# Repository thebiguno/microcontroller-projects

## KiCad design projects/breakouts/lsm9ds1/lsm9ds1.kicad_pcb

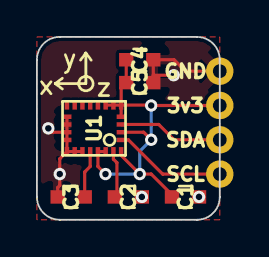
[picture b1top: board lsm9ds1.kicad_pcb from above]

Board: 2 copper layers, 10.2 x 10.2 mm, 7 parts (0 on the bottom side), 6 nets.

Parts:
C1, C2, C4: 100nF; C_0603
C3: 10nF; C_0603
C5: 10uF; C_0603
P1: CONN_01X04; Pin_Header_Straight_1x04
U1: LSM9DS1; LGA-24L

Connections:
+3V3: C1.1, C4.1, C5.1, P1.2, U1.1, U1.3, U1.5, U1.6, U1.7, U1.8, U1.22, U1.23
/SCL: P1.4, U1.2
/SDA: P1.3, U1.4
GND: C1.2, C2.2, C3.2, C4.2, C5.2, P1.1, U1.14, U1.15, U1.16, U1.17, U1.18, U1.19, U1.20
unnamed: C2.1, U1.24
unnamed: C3.1, U1.21

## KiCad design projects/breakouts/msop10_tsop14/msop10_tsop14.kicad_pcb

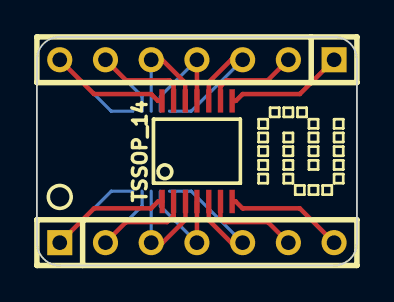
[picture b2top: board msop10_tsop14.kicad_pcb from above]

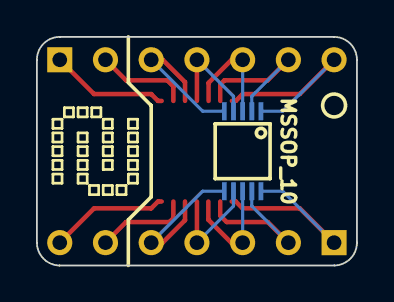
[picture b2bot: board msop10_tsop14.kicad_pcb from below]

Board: 2 copper layers, 17.8 x 12.7 mm, 6 parts (2 on the bottom side), 14 nets.

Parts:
K1, K2: PINS_7; SIL-7
K3: MSSOP_10; MSOP10-0.5
K4: TSSOP_14; TSSOP14
VAL: REF; DIGITALCAVE_LOGO
VAL#2: REF; DIGITALCAVE_LOGO

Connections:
unnamed: K2.2, K4.9
unnamed: K2.1, K4.8
unnamed: K1.7, K4.7
unnamed: K1.6, K4.6
unnamed: K2.3, K3.5, K4.10
unnamed: K1.5, K3.6, K4.5
unnamed: K1.4, K3.7, K4.4
unnamed: K2.4, K3.4, K4.11
unnamed: K2.5, K3.3, K4.12
unnamed: K2.6, K3.2, K4.13
unnamed: K2.7, K3.1, K4.14
unnamed: K1.3, K3.8, K4.3
unnamed: K1.2, K3.9, K4.2
unnamed: K1.1, K3.10, K4.1

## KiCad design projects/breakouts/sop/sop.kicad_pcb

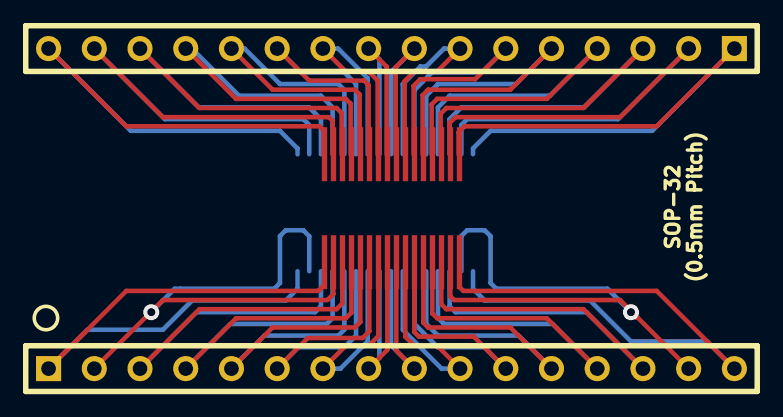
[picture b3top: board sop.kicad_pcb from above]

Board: 2 copper layers, 4 parts (1 on the bottom side), 32 nets.

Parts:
K1: PINS_32; SOP-32_05
K2: PINS_32; SOP-32_065
K3, K4: PINS_16; SIL-16

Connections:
unnamed: K1.32, K2.1, K4.16
unnamed: K1.31, K2.2, K4.15
unnamed: K1.30, K2.3, K4.14
unnamed: K1.29, K2.4, K4.13
unnamed: K1.28, K2.5, K4.12
unnamed: K1.27, K2.6, K4.11
unnamed: K1.26, K2.7, K4.10
unnamed: K1.25, K2.8, K4.9
unnamed: K1.15, K2.18, K3.15
unnamed: K1.5, K2.28, K3.5
unnamed: K1.14, K2.19, K3.14
unnamed: K1.4, K2.29, K3.4
unnamed: K1.24, K2.9, K4.8
unnamed: K1.23, K2.10, K4.7
unnamed: K1.13, K2.20, K3.13
unnamed: K1.3, K2.30, K3.3
unnamed: K1.22, K2.11, K4.6
unnamed: K1.12, K2.21, K3.12
unnamed: K1.2, K2.31, K3.2
unnamed: K1.21, K2.12, K4.5
unnamed: K1.11, K2.22, K3.11
unnamed: K1.1, K2.32, K3.1
unnamed: K1.20, K2.13, K4.4
unnamed: K1.10, K2.23, K3.10
unnamed: K1.19, K2.14, K4.3
unnamed: K1.9, K2.24, K3.9
unnamed: K1.18, K2.15, K4.2
unnamed: K1.8, K2.25, K3.8
unnamed: K1.17, K2.16, K4.1
unnamed: K1.7, K2.26, K3.7
unnamed: K1.16, K2.17, K3.16
unnamed: K1.6, K2.27, K3.6

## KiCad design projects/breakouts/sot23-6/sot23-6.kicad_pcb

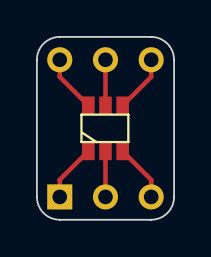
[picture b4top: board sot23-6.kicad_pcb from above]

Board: 2 copper layers, 7.6 x 10.2 mm, 3 parts (0 on the bottom side), 6 nets.

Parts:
K1: PINS_6; SOT23_6
K2, K3: PINS_3; SIL-3

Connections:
unnamed: K1.1, K2.1
unnamed: K1.2, K2.2
unnamed: K1.3, K2.3
unnamed: K1.4, K3.3
unnamed: K1.5, K3.2
unnamed: K1.6, K3.1

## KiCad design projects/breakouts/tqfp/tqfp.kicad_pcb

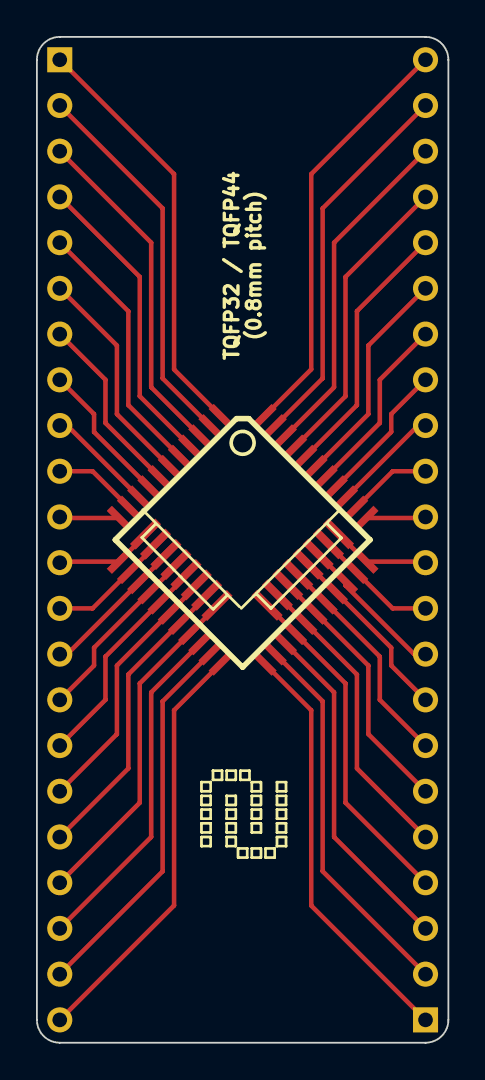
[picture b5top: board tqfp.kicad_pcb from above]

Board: 2 copper layers, 22.9 x 55.9 mm, 5 parts (0 on the bottom side), 16 nets.

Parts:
K1: PINS_44; TQFP44
K2, K3: PINS_22; SIL-18
K4: PINS_32; TQFP32
VAL: REF; DIGITALCAVE_LOGO

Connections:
unnamed: K1.30, K4.21
unnamed: K1.13, K4.10
unnamed: K1.32, K4.23
unnamed: K1.12, K4.9
unnamed: K1.31, K4.22
unnamed: K1.33, K4.24
unnamed: K1.29, K4.20
unnamed: K1.19, K4.16
unnamed: K1.28, K4.19
unnamed: K1.18, K4.15
unnamed: K1.27, K4.18
unnamed: K1.17, K4.14
unnamed: K1.26, K4.17
unnamed: K1.16, K4.13
unnamed: K1.15, K4.12
unnamed: K1.14, K4.11

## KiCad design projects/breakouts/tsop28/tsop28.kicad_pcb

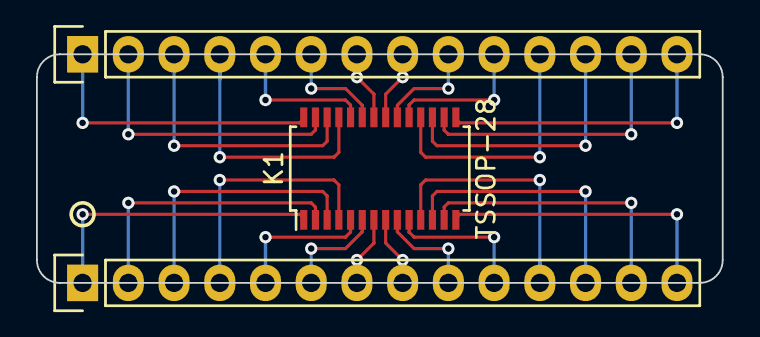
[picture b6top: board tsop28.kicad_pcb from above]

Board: 2 copper layers, 38.1 x 12.7 mm, 3 parts (0 on the bottom side), 28 nets.

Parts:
K1: TSSOP-28; TSSOP-28_4.4x9.7mm_Pitch0.65mm
K2, K3: DIP; Pin_Header_Straight_1x14

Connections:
unnamed: K1.1, K2.1
unnamed: K1.2, K2.2
unnamed: K1.3, K2.3
unnamed: K1.4, K2.4
unnamed: K1.5, K2.5
unnamed: K1.6, K2.6
unnamed: K1.7, K2.7
unnamed: K1.8, K2.8
unnamed: K1.9, K2.9
unnamed: K1.10, K2.10
unnamed: K1.11, K2.11
unnamed: K1.12, K2.12
unnamed: K1.13, K2.13
unnamed: K1.14, K2.14
unnamed: K1.15, K3.14
unnamed: K1.16, K3.13
unnamed: K1.17, K3.12
unnamed: K1.18, K3.11
unnamed: K1.19, K3.10
unnamed: K1.20, K3.9
unnamed: K1.21, K3.8
unnamed: K1.22, K3.7
unnamed: K1.23, K3.6
unnamed: K1.24, K3.5
unnamed: K1.25, K3.4
unnamed: K1.26, K3.3
unnamed: K1.27, K3.2
unnamed: K1.28, K3.1

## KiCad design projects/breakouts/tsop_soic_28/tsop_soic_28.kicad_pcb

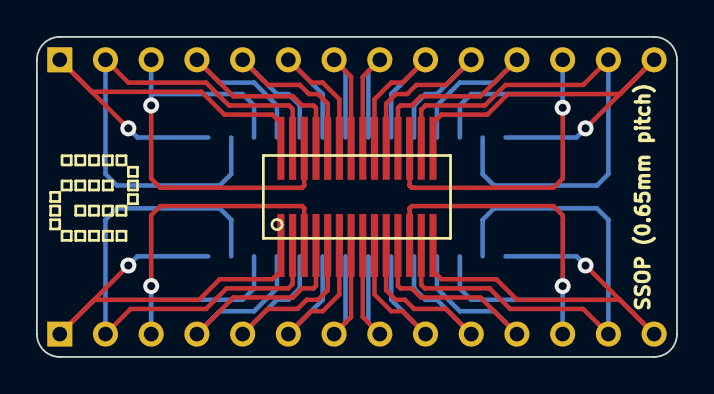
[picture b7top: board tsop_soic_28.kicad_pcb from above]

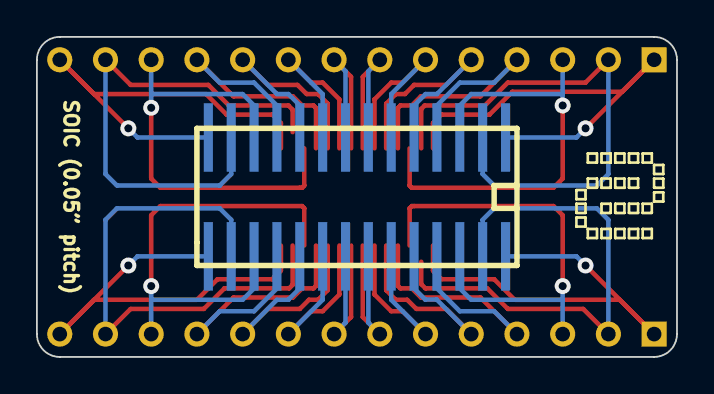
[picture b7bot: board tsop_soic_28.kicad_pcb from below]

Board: 2 copper layers, 35.6 x 17.8 mm, 6 parts (2 on the bottom side), 28 nets.

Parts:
K1: PINS_28; ssop-28
K2, K3: PINS_14; SIL-14
K4: PINS_28; SO28
VAL: REF; DIGITALCAVE_LOGO
VAL#2: REF; DIGITALCAVE_LOGO

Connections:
unnamed: K1.26, K3.3, K4.3
unnamed: K1.27, K3.2, K4.2
unnamed: K1.18, K3.11, K4.11
unnamed: K1.28, K3.1, K4.1
unnamed: K1.19, K3.10, K4.10
unnamed: K1.1, K2.1, K4.28
unnamed: K1.2, K2.2, K4.27
unnamed: K1.3, K2.3, K4.26
unnamed: K1.4, K2.4, K4.25
unnamed: K1.5, K2.5, K4.24
unnamed: K1.6, K2.6, K4.23
unnamed: K1.7, K2.7, K4.22
unnamed: K1.8, K2.8, K4.21
unnamed: K1.9, K2.9, K4.20
unnamed: K1.10, K2.10, K4.19
unnamed: K1.20, K3.9, K4.9
unnamed: K1.11, K2.11, K4.18
unnamed: K1.21, K3.8, K4.8
unnamed: K1.12, K2.12, K4.17
unnamed: K1.22, K3.7, K4.7
unnamed: K1.13, K2.13, K4.16
unnamed: K1.23, K3.6, K4.6
unnamed: K1.14, K2.14, K4.15
unnamed: K1.24, K3.5, K4.5
unnamed: K1.25, K3.4, K4.4
unnamed: K1.17, K3.12, K4.12
unnamed: K1.16, K3.13, K4.13
unnamed: K1.15, K3.14, K4.14

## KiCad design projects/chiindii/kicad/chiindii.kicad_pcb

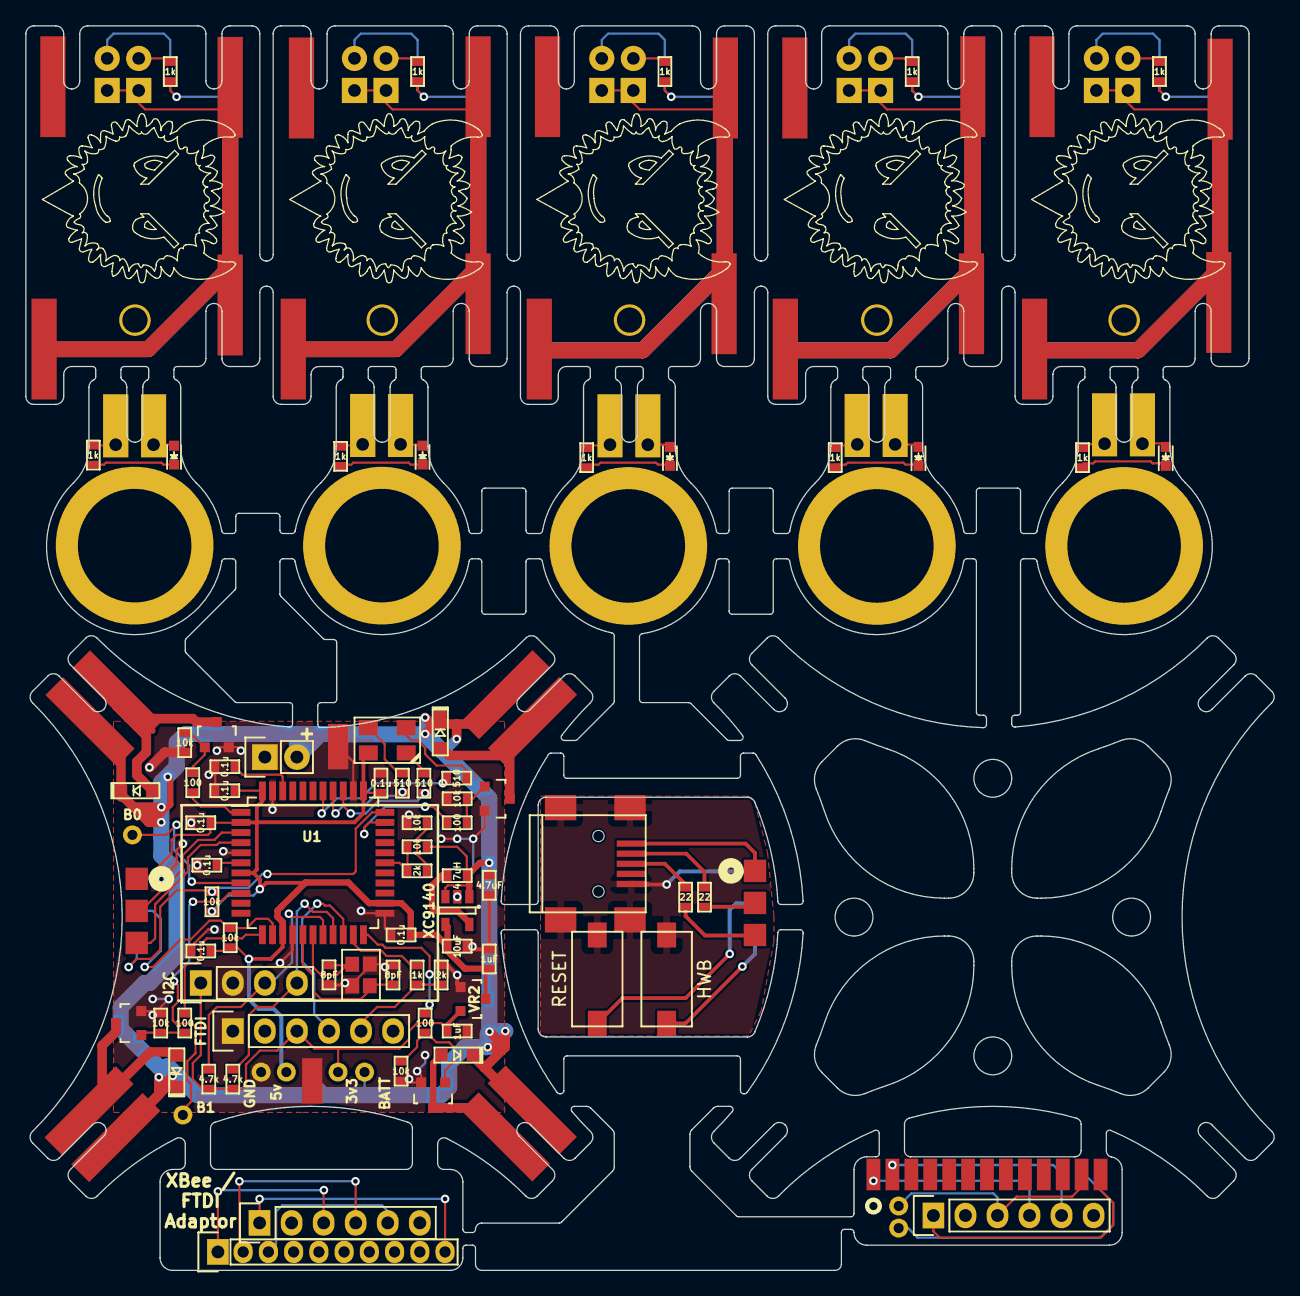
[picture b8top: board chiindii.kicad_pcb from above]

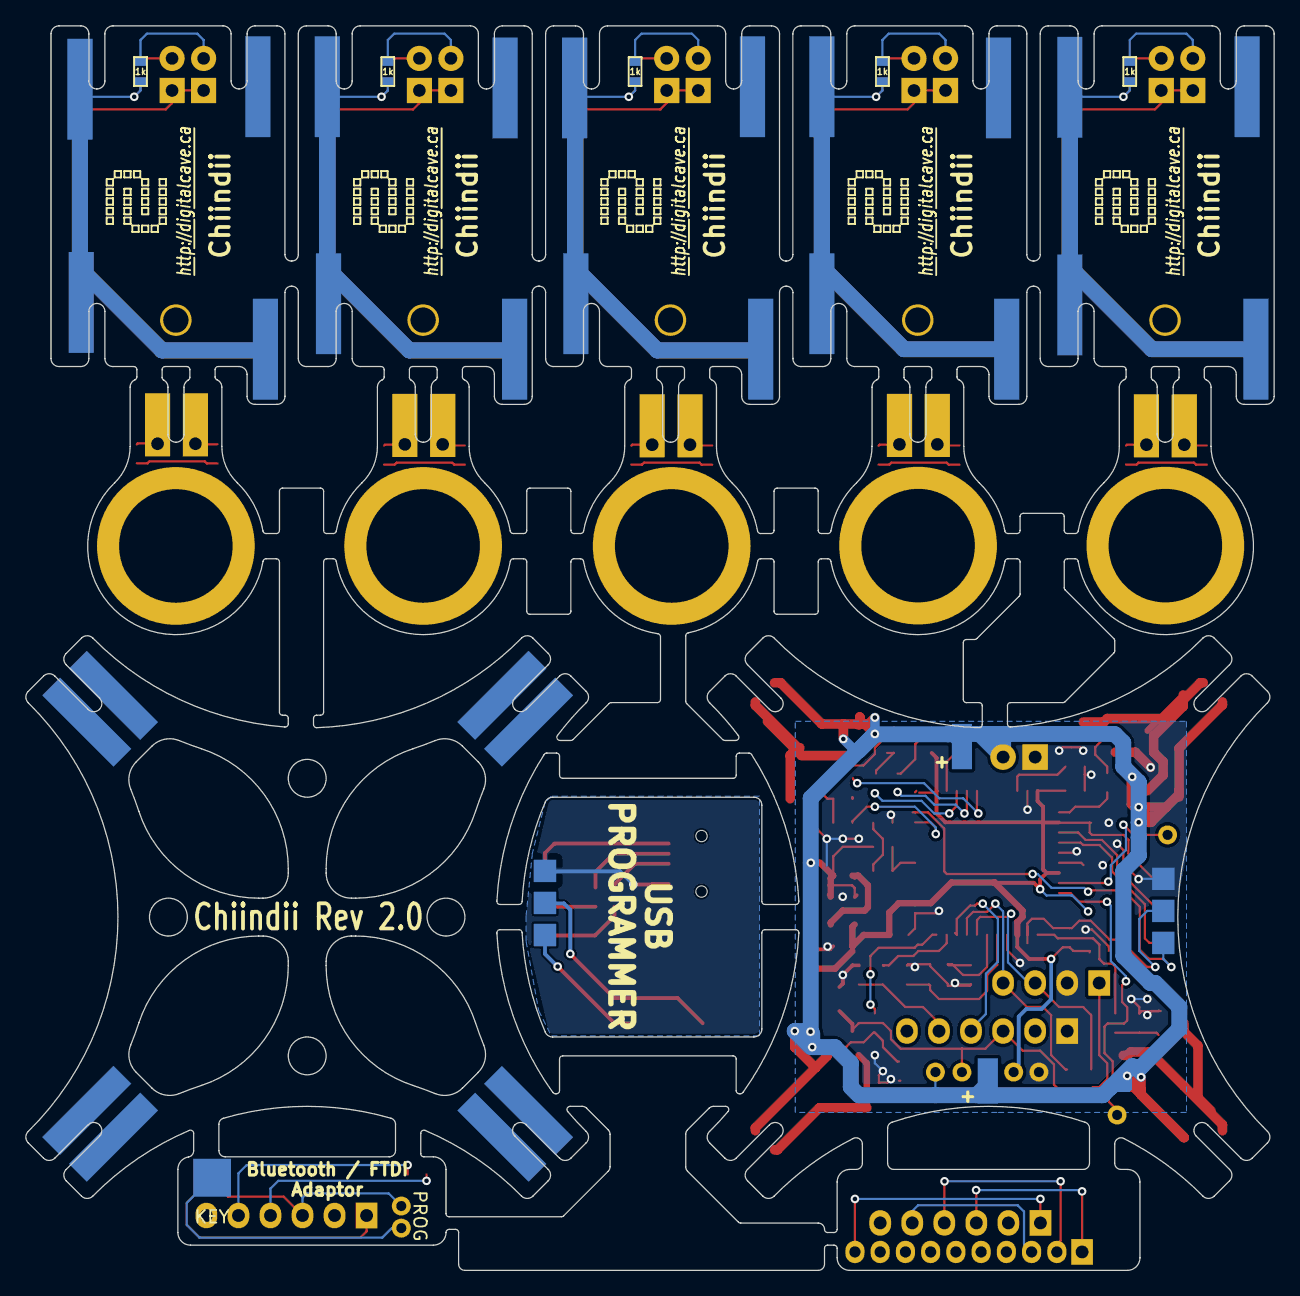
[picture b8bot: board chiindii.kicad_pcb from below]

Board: 2 copper layers, 98.9 x 98.6 mm, 154 parts (25 on the bottom side), 92 nets.

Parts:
C1, C2: 470uF; c_elec_6.3x5.8
C3: 4.7uF; SM0603_VALUE
C4: 10uF; SM0603_VALUE
C5, C6: 1uF; SM0603_VALUE
C7, C8: 8pF; SM0603_VALUE
C9, C10, C11, C12, C13, C14, C15: 0.1u; SM0603_VALUE
D1, D2, D3, D4: DSCHSMALL; SOD-323_DIODE
D5, D6, D7, D8, D9: LED; LED-0603
D10: RGB_LED_COMMON_ANODE_ALT1; LED_RGB_4-PLCC_ALT1
D11, D12, D13, D14, D15, D16, D17, D18, D19, D20: LED; LED-3MM
L1: 4.7uH; SM0603_VALUE
MP1, MP2, MP3, MP4, MP5: MOTOR; MOTOR_0820
MP6, MP9, MP12, MP15, MP18: GRAPHIC; DIGITALCAVE_LOGO
MP7, MP10, MP13, MP16, MP19: GRAPHIC; DIGITALCAVE_URL
MP8, MP11, MP14, MP17, MP20: HOLE; Pin_Header_Straight_1x01
P1: BATTERY; Pin_Header_Straight_1x02
P2: USB_OTG; USB_Mini-B
P3, P4, P6, P7: BODY_MOTOR_OUTPUT; H_JOINT
P5: PROG_CONN_A; ISP_EDGE
P8, P9, P10, P11, P12: V_MOTOR_IN; V_JOINT
P13, P14, P15, P16, P17, P18, P19, P20, P21, P22: V_MOTOR_OUT; V_JOINT
P23: 5v; Measurement_Point_Round-TH_Small
P24: 3v3; Measurement_Point_Round-TH_Small
P25: BATT; Measurement_Point_Round-TH_Small
P26: GND; Measurement_Point_Round-TH_Small
P27: FTDI; Pin_Header_Straight_1x06
P28, P29, P30, P31, P32: H_MOTOR_IN; H_JOINT_TH
P33: I2C; Pin_Header_Straight_1x04
P34, P35, P36, P37, P38: V_BAT_SUPPORT; V_JOINT
P39, P40, P41, P42: H_BAT_SUPPORT; H_JOINT
P43: PROG_CONN_B; ISP_EDGE
P44: XBEE_FTDI; Pin_Header_Straight_1x06
P45: XBEE; Pin_Header_Straight_1x10
P46: BT_FTDI; Pin_Header_Straight_1x06
P47: HC-05 / HM-10; Pin_Header_Straight_1x13
P48: PROG; Pin_Header_Straight_1x02
P49: KEY; Pin_Header_Straight_1x01
P50: B0; Measurement_Point_Round-TH_Small
P51: B1; Measurement_Point_Round-TH_Small
Q1, Q2, Q3, Q4: Q_NMOS_GSD; SOT-23
R1, R2, R7, R8: 100; SM0603_VALUE
R3, R4, R9, R10, R17, R18, R19, R25: 10k; SM0603_VALUE
R5, R6: 22; SM0603_VALUE
R11, R12, R13, R14, R15, R23, R28, R29, R30, R31, R32, R33, R34, R35, R36, R37: 1k; SM0603_VALUE
R16, R26: 2k; SM0603_VALUE
R20, R21, R22: 510; SM0603_VALUE
R24, R27: 4.7k; SM0603_VALUE
SW1: RESET; SW_6x3
SW2: HWB; SW_6x3
U1: ATMEGA32U4-A; TQFP-44_10x10mm_Pitch0.8mm
VR1: XC9140; SOT-23-5
VR2: MCP1702; SOT-23
X1: 16MHz; CRYSTAL_SMD_2.5x2

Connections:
+3V3: C6.1, P24.1, P27.3, P33.1, R24.2, R27.2, VR2.2
+5V: C4.1, C5.1, C11.2, C12.2, C13.2, C14.2, C15.2, D10.1, P23.1, P43.1, R19.2, R25.1, U1.2, U1.7, U1.14, U1.24, U1.34, U1.44, VR1.4, VR2.3
+BATT: C1.1, C2.1, C3.1, D1.2, D2.2, D3.2, D4.2, L1.1, P1.2, P3.1, P4.1, P6.1, P7.1, P25.1, R18.2, VR1.1, VR1.3
/B0: P50.1, U1.8
/B1: P51.1, U1.9
/BATT_ADC: R16.2, R18.1, U1.28
/D+: P43.5, U1.4
/D-: P43.3, U1.3
/DC+: P2.3, R5.1
/DC-: P2.2, R6.1
/DP+: P5.5, R5.2
/DP-: P5.3, R6.2
/HWB: P43.6, R25.2, U1.33
/MOTOR1: R1.1, U1.1
/MOTOR2: R7.1, U1.22
/MOTOR3: R2.1, U1.32
/MOTOR4: R8.1, U1.12
/PRG_GND: P2.5, P2.6, P5.2, SW1.1, SW2.1
/RADIO_RX: P27.5, R23.1, R26.2
/RADIO_TX: P27.4, U1.20
/RESET: P43.4, R19.1, U1.13
/SCL: P33.3, R24.1, U1.18
/SDA: P33.4, R27.1, U1.19
/X+: C7.1, U1.17, X1.1
/X-: C8.1, U1.16, X1.3
GND: C1.2, C2.2, C3.2, C4.2, C5.2, C6.2, C7.2, C8.2, C9.2, C10.2, C11.1, C12.1, C13.1, C14.1, C15.1, P1.1, P26.1, P27.1, P33.2, P43.2, Q1.2, Q2.2, Q3.2, Q4.2, R3.1, R4.1, R9.1, R10.1, R17.1, R26.1, U1.5, U1.15, U1.23, U1.35, U1.43, VR1.2, VR2.1, X1.2, X1.4
unnamed: C9.1, U1.6
unnamed: C10.1, U1.42
unnamed: D1.1, P3.2, Q1.3
unnamed: D2.1, P4.2, Q2.3
unnamed: D3.1, P6.2, Q3.3
unnamed: D4.1, P7.2, Q4.3
unnamed: D5.1, R11.2
unnamed: D5.2, P28.1
unnamed: D6.1, R12.2
unnamed: D6.2, P29.1
unnamed: D7.1, R13.2
unnamed: D7.2, P30.1
unnamed: D8.1, R14.2
unnamed: D8.2, P31.1
unnamed: D9.1, R15.2
unnamed: D9.2, P32.1
unnamed: D10.2, R22.1
unnamed: D10.3, R21.1
unnamed: D10.4, R20.1
unnamed: D11.1, D12.1, P8.2, P13.2, P18.2
unnamed: D11.2, R28.1
unnamed: D12.2, R29.1
unnamed: D13.1, D14.1, P9.2, P14.2, P19.2
unnamed: D13.2, R30.1
unnamed: D14.2, R31.1
unnamed: D15.1, D16.1, P10.2, P15.2, P20.2
unnamed: D15.2, R32.1
unnamed: D16.2, R33.1
unnamed: D17.1, D18.1, P11.2, P16.2, P21.2
unnamed: D17.2, R34.1
unnamed: D18.2, R35.1
unnamed: D19.1, D20.1, P12.2, P17.2, P22.2
unnamed: D19.2, R36.1
unnamed: D20.2, R37.1
unnamed: L1.2, VR1.5
unnamed: P2.1, P5.1
unnamed: P5.4, SW1.2
unnamed: P5.6, SW2.2
unnamed: P10.1, P15.1, P20.1, R32.2, R33.2
unnamed: P11.1, P16.1, P21.1, R34.2, R35.2
unnamed: P12.1, P17.1, P22.1, R36.2, R37.2
unnamed: P8.1, P13.1, P18.1, R28.2, R29.2
unnamed: P9.1, P14.1, P19.1, R30.2, R31.2
unnamed: P28.2, R11.1
unnamed: P29.2, R12.1
unnamed: P30.2, R13.1
unnamed: P31.2, R14.1
unnamed: P32.2, R15.1
unnamed: P44.1, P45.10
unnamed: P44.3, P45.1
unnamed: P44.4, P45.2
unnamed: P44.5, P45.3
unnamed: P46.1, P47.13
unnamed: P46.3, P47.12, P48.1
unnamed: P46.4, P47.1
unnamed: P46.5, P47.2
unnamed: P48.2, P49.1
unnamed: Q1.1, R1.2, R3.2
unnamed: Q2.1, R2.2, R4.2
unnamed: Q3.1, R7.2, R9.2
unnamed: Q4.1, R8.2, R10.2
unnamed: R16.1, R17.2
unnamed: R20.2, U1.38
unnamed: R21.2, U1.37
unnamed: R22.2, U1.36
unnamed: R23.2, U1.21
